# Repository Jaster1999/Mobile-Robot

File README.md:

# Mobile-Robot
Code base for the self navigating robot

Things to do:
- produce countour box for robot
- create grid
- produce astar algorithm
- test and test

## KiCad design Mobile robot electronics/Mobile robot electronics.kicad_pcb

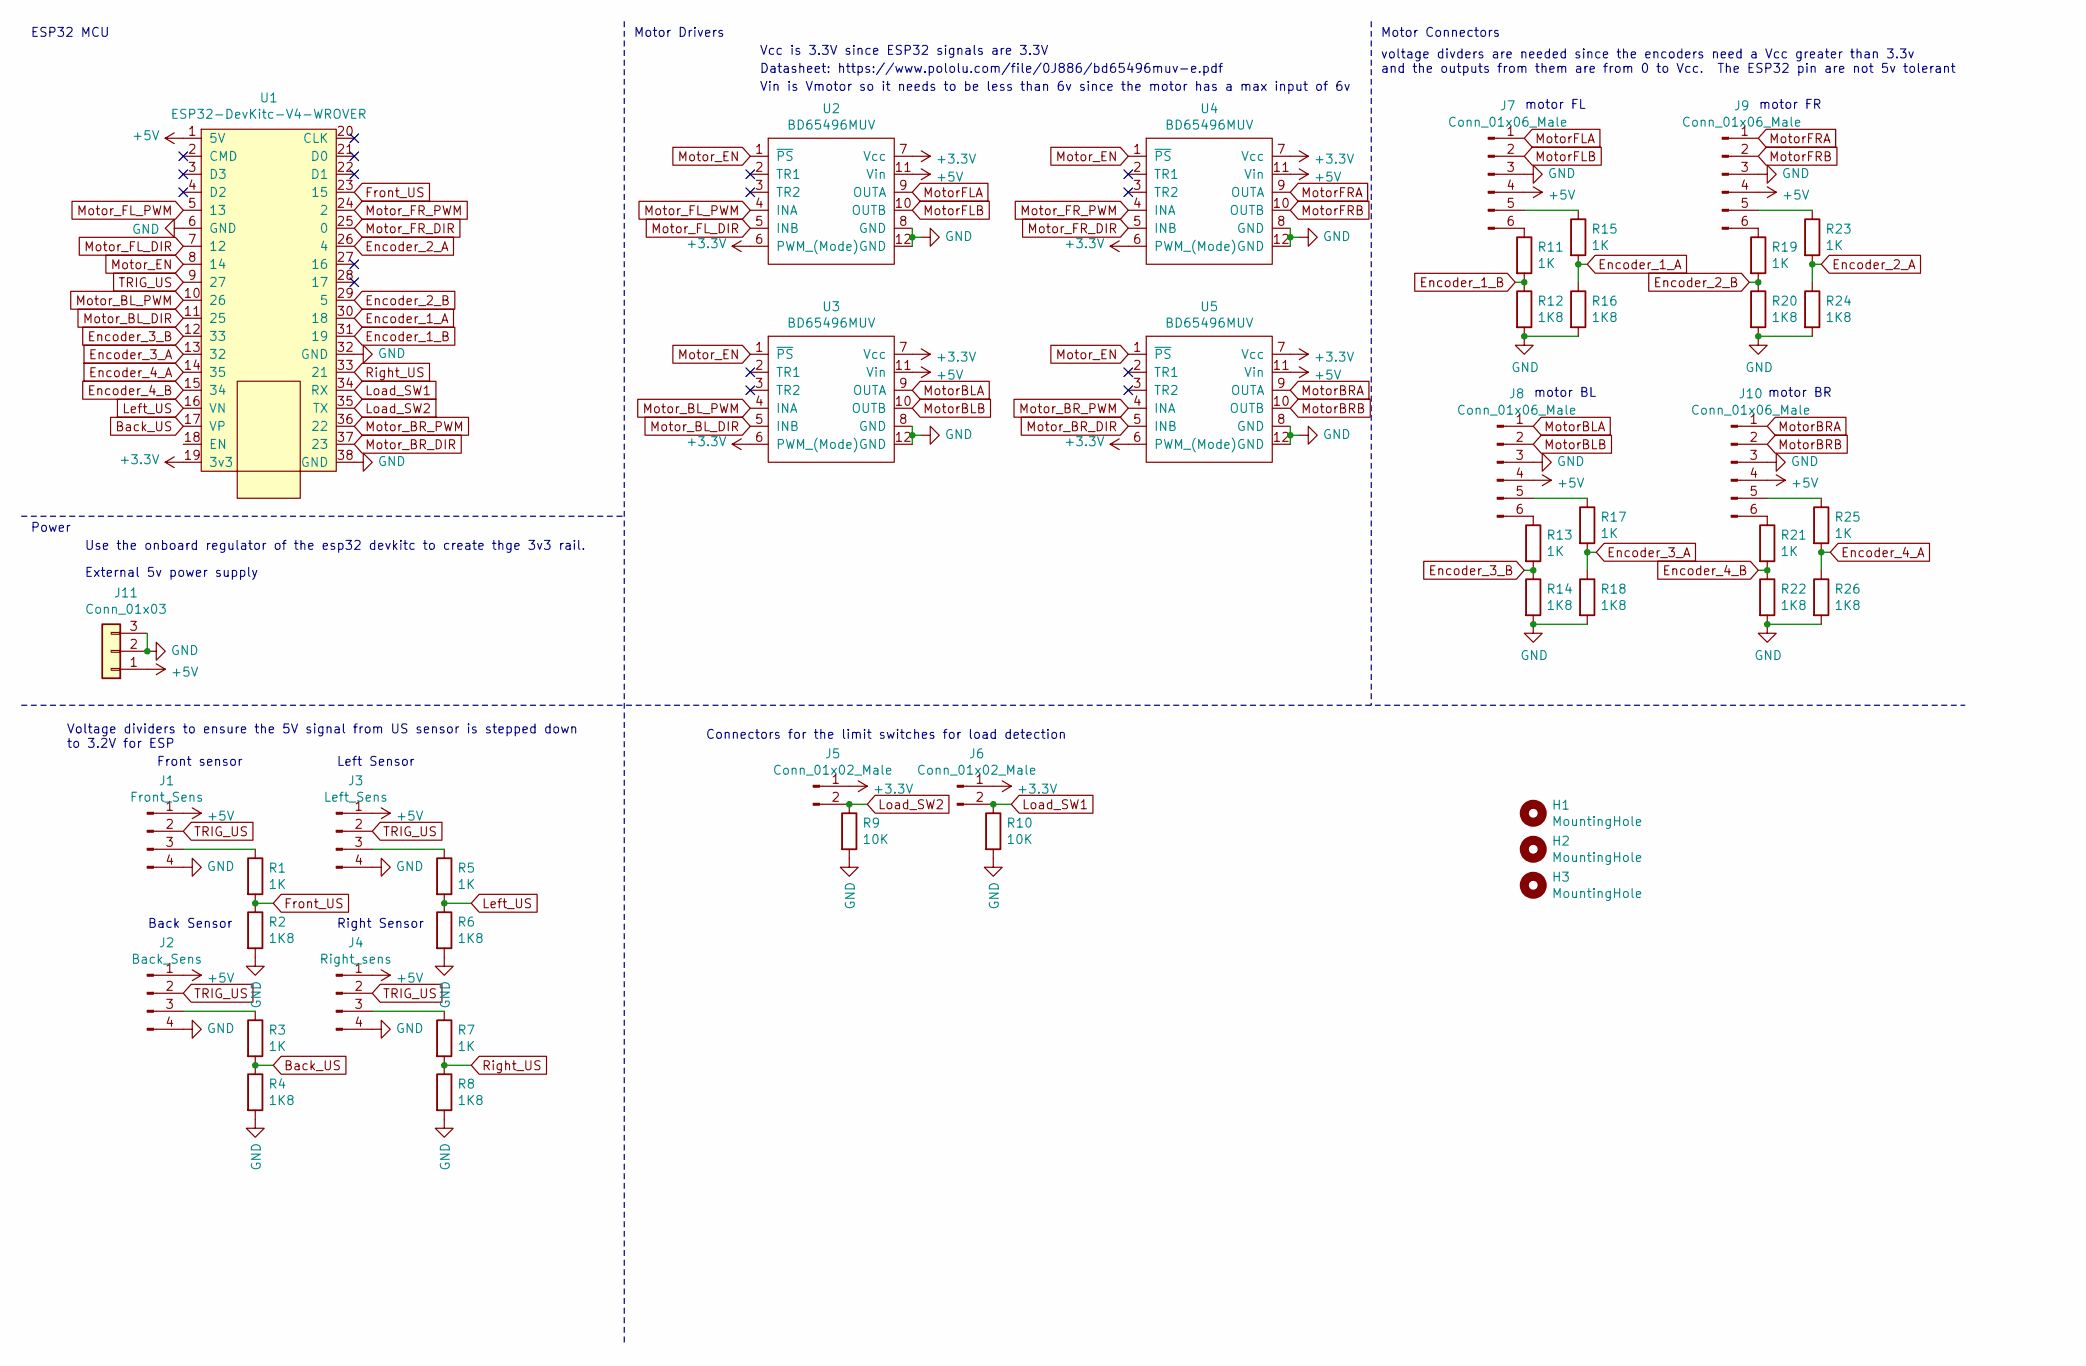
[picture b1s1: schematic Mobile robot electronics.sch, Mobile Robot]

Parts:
H1, H2, H3: MountingHole; MountingHole_4.3mm_M4
J1: Front_Sens; PinHeader_1x04_P2.54mm_Vertical
J2: Back_Sens; PinHeader_1x04_P2.54mm_Vertical
J3: Left_Sens; PinHeader_1x04_P2.54mm_Vertical
J4: Right_sens; PinHeader_1x04_P2.54mm_Vertical
J5, J6: Conn_01x02_Male; PinHeader_1x02_P2.54mm_Vertical
J7, J8, J9, J10: Conn_01x06_Male; PinHeader_1x06_P2.54mm_Vertical
J11: Conn_01x03; BarrelJack_Horizontal
R1, R3, R5, R7, R11, R13, R15, R17, R19, R21, R23, R25: 1K; R_Axial_DIN0207_L6.3mm_D2.5mm_P10.16mm_Horizontal
R2, R4, R6, R8, R12, R14, R16, R18, R20, R22, R24, R26: 1K8; R_Axial_DIN0207_L6.3mm_D2.5mm_P10.16mm_Horizontal
R9, R10: 10K; R_Axial_DIN0207_L6.3mm_D2.5mm_P10.16mm_Horizontal
U1: ESP32-DevKitc-V4-WROVER; ESP32-DevKitC-V4-WROVER
U2, U3, U4, U5: BD65496MUV; BD65496MUV_Carrier

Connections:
+3V3: J5.1, J6.1, U1.19 (3v3), U2.6 (PWM_(Mode)), U2.7 (Vcc), U3.6 (PWM_(Mode)), U3.7 (Vcc), U4.6 (PWM_(Mode)), U4.7 (Vcc), U5.6 (PWM_(Mode)), U5.7 (Vcc)
+5V: J1.1, J2.1, J3.1, J4.1, J7.4, J8.4, J9.4, J10.4, J11.1, U1.1 (5V), U2.11 (Vin), U3.11 (Vin), U4.11 (Vin), U5.11 (Vin)
Back_US: R3.2, R4.1, U1.17 (VP)
Encoder_1_A: R15.2, R16.1, U1.30 (18)
Encoder_1_B: R11.2, R12.1, U1.31 (19)
Encoder_2_A: R23.2, R24.1, U1.26 (4)
Encoder_2_B: R19.2, R20.1, U1.29 (5)
Encoder_3_A: R17.2, R18.1, U1.13 (32)
Encoder_3_B: R13.2, R14.1, U1.12 (33)
Encoder_4_A: R25.2, R26.1, U1.14 (35)
Encoder_4_B: R21.2, R22.1, U1.15 (34)
Front_US: R1.2, R2.1, U1.23 (15)
GND: J1.4, J2.4, J3.4, J4.4, J7.3, J8.3, J9.3, J10.3, J11.2, J11.3, R2.2, R4.2, R6.2, R8.2, R9.2, R10.2, R12.2, R14.2, R16.2, R18.2, R20.2, R22.2, R24.2, R26.2, U1.6 (GND), U1.32 (GND), U1.38 (GND), U2.8 (GND), U2.12 (GND), U3.8 (GND), U3.12 (GND), U4.8 (GND), U4.12 (GND), U5.8 (GND), U5.12 (GND)
Left_US: R5.2, R6.1, U1.16 (VN)
Load_SW1: J6.2, R10.1, U1.34 (RX)
Load_SW2: J5.2, R9.1, U1.35 (TX)
MotorBLA: J8.1, U3.9 (OUTA)
MotorBLB: J8.2, U3.10 (OUTB)
MotorBRA: J10.1, U5.9 (OUTA)
MotorBRB: J10.2, U5.10 (OUTB)
MotorFLA: J7.1, U2.9 (OUTA)
MotorFLB: J7.2, U2.10 (OUTB)
MotorFRA: J9.1, U4.9 (OUTA)
MotorFRB: J9.2, U4.10 (OUTB)
Motor_BL_DIR: U1.11 (25), U3.5 (INB)
Motor_BL_PWM: U1.10 (26), U3.4 (INA)
Motor_BR_DIR: U1.37 (23), U5.5 (INB)
Motor_BR_PWM: U1.36 (22), U5.4 (INA)
Motor_EN: U1.8 (14), U2.1 (~PS), U3.1 (~PS), U4.1 (~PS), U5.1 (~PS)
Motor_FL_DIR: U1.7 (12), U2.5 (INB)
Motor_FL_PWM: U1.5 (13), U2.4 (INA)
Motor_FR_DIR: U1.25 (0), U4.5 (INB)
Motor_FR_PWM: U1.24 (2), U4.4 (INA)
unnamed: J1.3, R1.1
unnamed: J2.3, R3.1
unnamed: J3.3, R5.1
unnamed: J4.3, R7.1
unnamed: J7.5, R15.1
unnamed: J7.6, R11.1
unnamed: J8.5, R17.1
unnamed: J8.6, R13.1
unnamed: J9.5, R23.1
unnamed: J9.6, R19.1
unnamed: J10.5, R25.1
unnamed: J10.6, R21.1
Right_US: R7.2, R8.1, U1.33 (21)
TRIG_US: J1.2, J2.2, J3.2, J4.2, U1.9 (27)

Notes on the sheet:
Vcc is 3.3V since ESP32 signals are 3.3V
Datasheet: https://www.pololu.com/file/0J886/bd65496muv-e.pdf
Vin is Vmotor so it needs to be less than 6v since the motor has a max input of 6v
motor FL
motor FR
motor BL
motor BR
voltage divders are needed since the encoders need a Vcc greater than 3.3v and the outputs from them are from 0 to Vcc. The ESP32 pin are not 5v tolerant
ESP32 MCU
Motor Drivers
Motor Connectors
Front sensor
Back Sensor
Left Sensor
Right Sensor
Voltage dividers to ensure the 5V signal from US sensor is stepped down to 3.2V for ESP
Connectors for the limit switches for load detection
Use the onboard regulator of the esp32 devkitc to create thge 3v3 rail.
External 5v power supply
Power

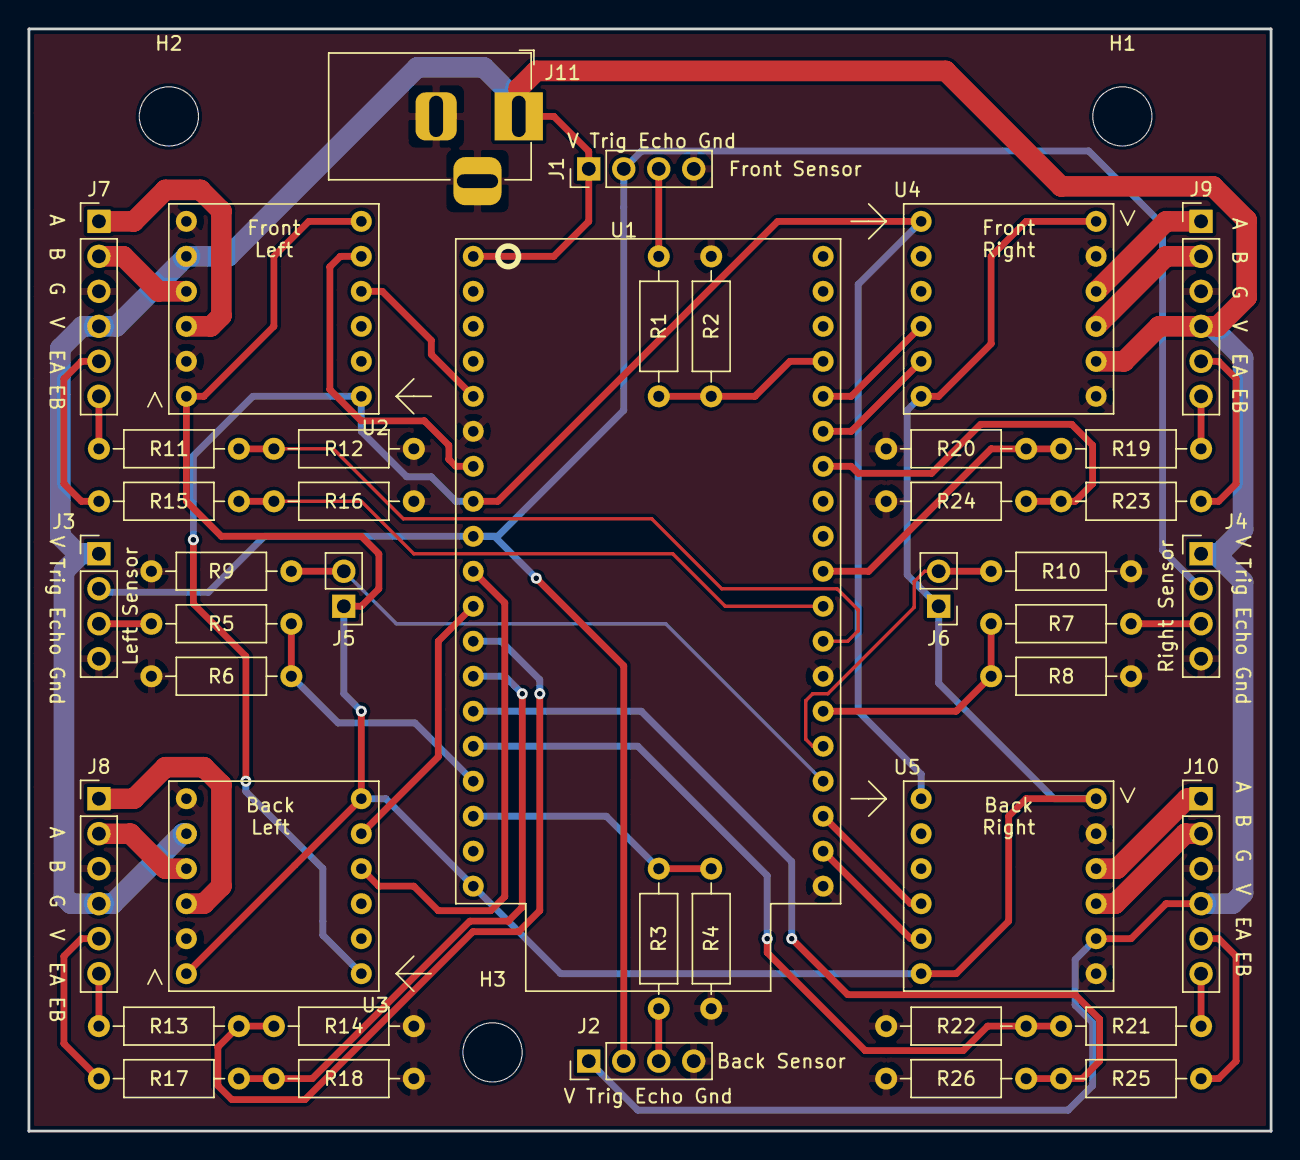
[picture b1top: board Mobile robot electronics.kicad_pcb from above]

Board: 2 copper layers, 90.2 x 80.0 mm, 45 parts (0 on the bottom side), 47 nets.

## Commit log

2021-04-12 uploaded the schematic work from kicad
2021-04-12 Initial HSV filter for object detection
    real time video HSV segementation of all non grey objects i.e. not the floor.
2021-04-12 added to schematic:
    motor connectors, connections for the motor drivers, started the headers for the ultrasonics
2021-04-13 HSVSegFilter.py
2021-04-20 First upload of the mobile robot motor control on the ESP32-S2 Saola
2021-04-20 yeah boi
2021-04-21 Initial commit of project folder
    Includes initialised Bluetooth and motor control
2021-04-21 Delete HSVSegFilter.py
    Cleaning up the folder
2021-04-21 Update todo list
2021-04-21 Add ultrasonic sensor pins
    Still practicing with git from vscode
2021-04-25 added a correct part for ESP32 devkitc v4 wrover
2021-04-25 created symbol for esp32 devkitc v4
2021-04-25 Modify pin defs for different esp32 board
    Modify pin defs,
    Add stop to motors
    make a global freq variable and adjust code
2021-04-26 Finished the schematic...for now, started PCB
2021-04-26 routed tracks for pcb, changed some pins on esp
2021-04-28 added mounting holes for PCB
2021-04-29 Reverse left turn functions
2021-04-30 made motor traces thicker, added silk screen stuff
2021-05-03 created gerbers for ordering
2021-05-06 Functionised filter
2021-05-12 Get PC bluetooth working
2021-05-13 Functionised the filters
2021-05-13 generated BOM
2021-05-13 Make PC master version
2021-05-13 Platformio update
2021-05-13 File loc change
2021-05-13 ljkdsnflkjxn
2021-05-13 asasasas
2021-05-13 Change pin defs, adjust frequency
2021-05-13 ESP32 PC bluetooth serial master confirmed
2021-05-13 Clean up some comments
2021-05-13 Clean up comments, change MAC address
2021-05-17 Modify baud rate
2021-05-17 duty and add rotate cw/ccw
2021-05-17 step file of pcb
2021-05-17 change baud and try reconnect if disconnect
2021-05-17 lots of stuff
2021-05-17 Cleaned code
2021-05-17 got the python to serial link working
2021-05-17 Bluetooth reconnectability fixed
2021-05-18 Add hardware timer interrupt capability
2021-05-18 small comment changes
2021-05-18 minor changes
2021-05-18 Angle stuff
2021-05-18 Critical upgrades
2021-05-18 Up the minimum duty
2021-05-18 Fully functional cv and nav
2021-05-18 Add useful comments
2021-05-18 more comments
2021-05-18 serial stuff works
2021-05-18 Collated nav and cv code
2021-05-18 Collated code
2021-05-18 Add serial control yeetbot
2021-05-18 duty speed change
2021-05-19 Code that worked for the presentation!!!
2021-05-19 Critiacal Updates, code that worked for presentation
2021-09-06 Initial Commit
    Initial PlatformIO project, includes stepper and servo initialization. Hybrid of gantry control and HISS.
2021-09-06 Update some comments
2021-09-06 Make homing mandatory on startup
2021-09-06 Add serial monitoring
2021-09-06 Add stepper Z axis control
2021-09-06 make z axis must be homed before being able to be operated
2021-09-10 remove old pin defs
2021-09-11 Created Schematic for Motor control of manipulator
2021-09-11 Update pin defs to match schematic and ass joint4
2021-09-25 changed some pin defs
2021-10-12 Redesigned the Chassis
2021-10-12 Updated the CAD files and made new Step file
2021-10-13 Cut DXFs for new robot
2021-10-21 Made Serial interrupt driven
    I have removed the delay issue from the stepper code and have made it interrupt driven. If at anytime the # character, followed by enter, is received it will stop the stepper motor. Not sure how we c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
    I still need to implement the ability to send over multiple motor/joint commands in one message like how we did for gantry system.
    I also updated to use a RX and TX buffer (char array) rather than a "s
2021-10-22 Added Servo speed control
    Used Timer 2 in CTC mode to compare with comparator A. On match, an ISR runs. The ISR will increment the Servos closer to the setpoints. Currently the ISR runs every 8.128ms
2021-10-22 Found culprit of servo noise issue
    Pin attachment on servo for joint 4 was incorrect
2021-10-23 increased time between servo position updates
2021-10-23 Added EEPROM storage of previous joint angles
2021-10-23 Put the servo init into stepper homing function
    Not sure if this is the right idea, need to test it.
2021-10-23 Tried to make a gitignore
2021-10-24 Started work on Kinematics python stuff
    Slight error somewhere
2021-10-24 Kinematics work properly :)
2021-10-24 Added validator to the servo and stepper targets
    When setting the servo angle or stepper move target, the validator checks to see if the number received is a valid number. Also added the conversion from mm to steps for stepper motor. Also changed t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
2021-10-24 slight bug to fix from previous commit
2021-10-24 fixed angle validator function
    Might need some more work to ensure the servo angle matches the joint angle direction
2021-10-25 added a gitignore
2021-10-25 Made some CAD parts
    Made a nut for AL Ext, corner piece, Zaxis Mount plate, Zaxis to joint 2 mount plate and a new fruit basket
2021-10-25 made second half of fruit basket 2.0
    I dun fucked up
2021-10-25 Increased clearance on nut model
2021-10-26 fixed setpoint init bug
2021-10-26 Init additions to stop going to 0
2021-10-26 integrated MR code
2021-10-26 tried adding goal setting
2021-10-26 Change z limit switch pin and delay in homing
2021-10-26 added goal setting code
2021-10-26 Started Testing with camera
2021-10-27 Added angle to orientation function
2021-10-27 general fuckery
2021-10-27 serial for manipulator
2021-10-27 Added distance validator
2021-10-27 update Z axis
2021-10-27 Justin Testing stuff
2021-10-27 adjusted timeout on timer
2021-10-27 set to home to 90º
2021-10-27 working with mobile robot
2021-10-27 implementation fo working manipulator UI
2021-10-27 Inetgrated some of the CV with manip control
2021-10-27 Change timer overflow to 100ms
2021-10-27 Found the bug and solved
    code now looks for the \n and \r character to indicate the end of the line
2021-10-27 Stanley Doing shid
2021-10-27 minor tweak to RXbuffer
2021-10-28 UI from demo
2021-10-28 Committing what is on my laptop - Jack
